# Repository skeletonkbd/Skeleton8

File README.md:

# Skeleton8

 This is a 4x2 macropad assuming PCBA with stacked acrylic case.

### Firmware here

https://github.com/skeletonkbd/qmk_firmware/tree/Skeleton8/keyboards/skeletonkbd/skeleton8

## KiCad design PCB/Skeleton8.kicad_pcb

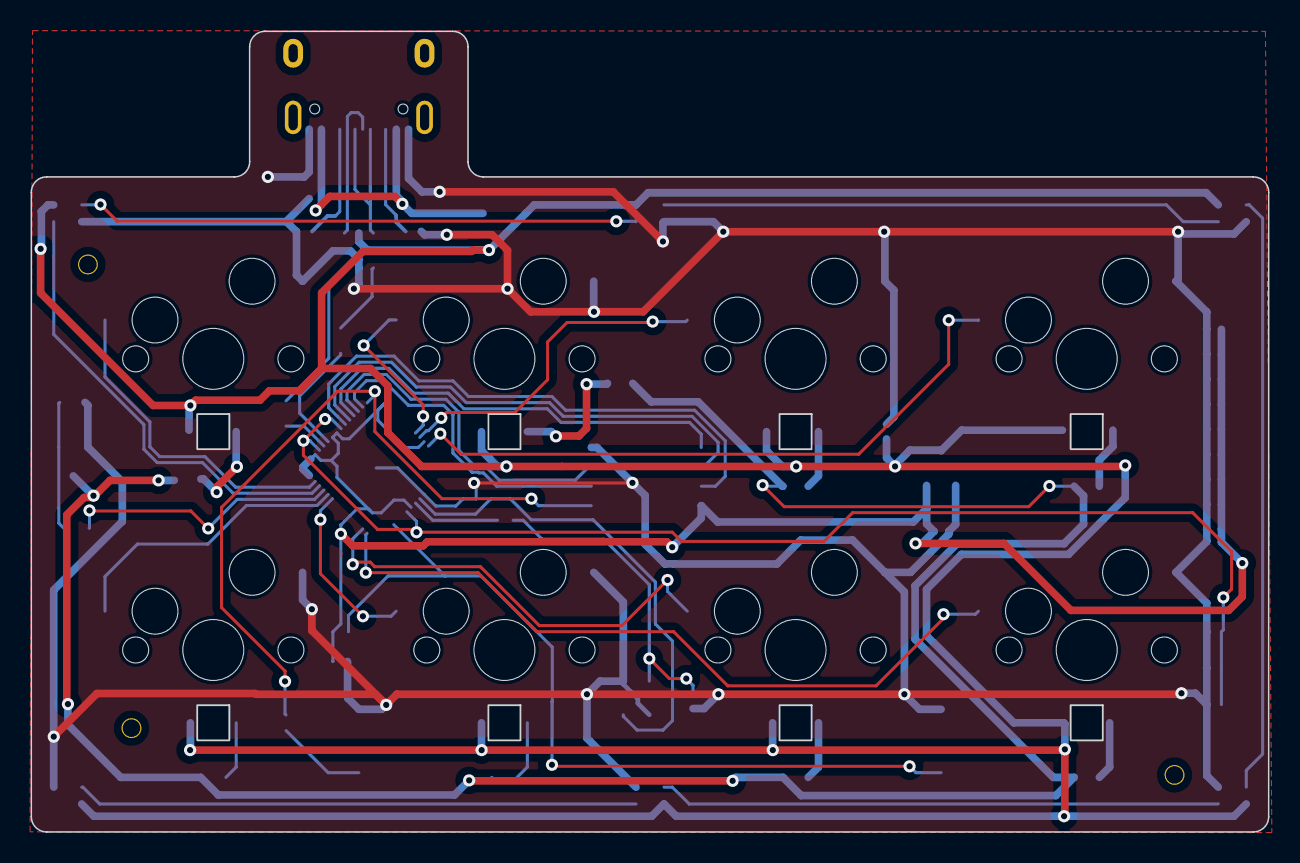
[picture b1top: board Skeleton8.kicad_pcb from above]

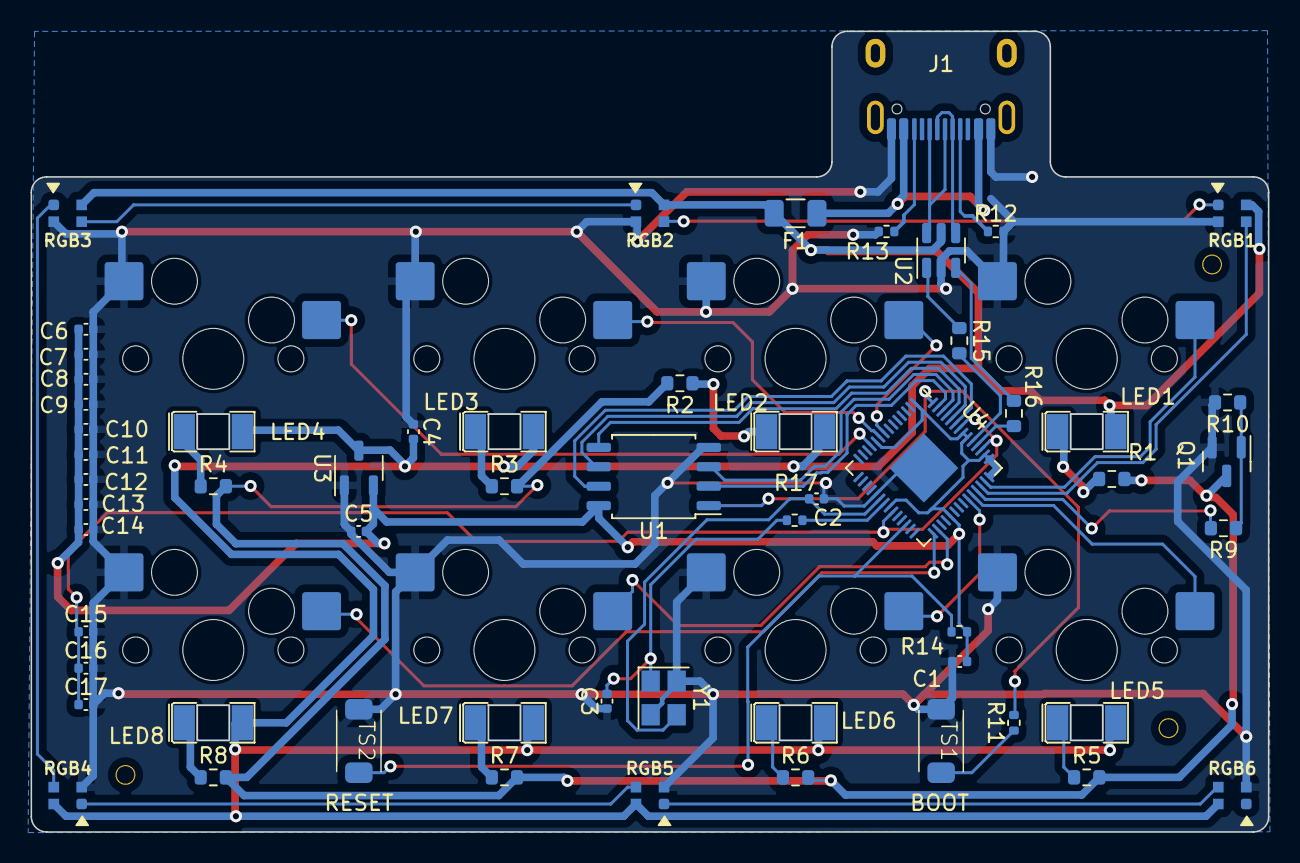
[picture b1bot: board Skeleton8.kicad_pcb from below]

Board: 2 copper layers, 80.9 x 52.4 mm, 69 parts (66 on the bottom side), 49 nets.

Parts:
C1, C8, C9, C10, C11, C12, C13, C14, C16, C17: 100nF; C_0402_1005Metric
C2, C3: 22pF; C_0402_1005Metric
C4, C5, C7, C15: 1uF; C_0402_1005Metric
C6: 10uF; C_0402_1005Metric
F1: 500mA; Fuse_1206_3216Metric
H1, H2, H3: Hole; ToolingHole
J1: TYPE-C-31-M-12; USB_C_Receptacle_Hroparts_TYPE-C-31-M-12
LED1, LED2, LED3, LED4, LED5, LED6, LED7, LED8: LTW-C230DS
Q1: SI2302; SOT-23
R1, R2, R3, R4, R5, R6, R7, R8: 150; R_0603_1608Metric
R9: 33; R_0603_1608Metric
R10: 10k; R_0603_1608Metric
R11, R14, R17: 1k; R_0402_1005Metric
R12, R13: 5k1; R_0402_1005Metric
R15, R16: 27; R_0603_1608Metric
RGB1, RGB2, RGB3, RGB4, RGB5, RGB6: WS2812B-2020; LED_WS2812_2020
SW1, SW2, SW3, SW4, SW5, SW6, SW7, SW8: SW_Push; MX-Hotswap-1U
TS1, TS2: SW_Push; TS-1088
U1: W25Q128JVS; SOIC-8_5.23x5.23mm_P1.27mm
U2: USBLC6-2SC6; SOT-23-6
U3: XC6206PxxxMR; SOT-23-3
U4: RP2040; QFN-56-1EP_7x7mm_P0.4mm_EP3.2x3.2mm
Y1: 12MHz; Crystal_SMD_3225-4Pin_3.2x2.5mm

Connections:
+1V1: C15.1, C16.1, C17.1, U4.23 (DVDD), U4.45 (VREG_VOUT), U4.50 (DVDD)
+3V3: C1.1, C5.2, C6.1, C7.1, C8.1, C9.1, C10.1, C11.1, C12.1, C13.1, C14.1, R14.1, U1.8 (VCC), U3.2 (VO), U4.1 (IOVDD), U4.10 (IOVDD), U4.22 (IOVDD), U4.33 (IOVDD), U4.42 (IOVDD), U4.43 (ADC_AVDD), U4.44 (VREG_IN), U4.48 (USB_VDD), U4.49 (IOVDD)
+5V: C4.2, F1.2, LED1.2 (A), LED2.2 (A), LED3.2 (A), LED4.2 (A), LED5.2 (A), LED6.2 (A), LED7.2 (A), LED8.2 (A), RGB1.4 (VDD), RGB2.4 (VDD), RGB3.4 (VDD), RGB4.4 (VDD), RGB5.4 (VDD), RGB6.4 (VDD), U2.5 (VBUS), U3.3 (VI)
/CC1: J1.A5 (CC1), R12.1
/CC2: J1.B5 (CC2), R13.1
/D_+: R15.2, U4.47 (USB_DP)
/D_-: R16.2, U4.46 (USB_DM)
/XTAL_O: C3.2, R17.1, Y1.1
/~USB_BOOT: R11.1, TS1.2
CS: R11.2, U1.1 (~CS), U4.56 (QSPI_SS)
D_N: R16.1, U2.3 (I/O2)
D_P: R15.1, U2.1 (I/O1)
D_USB_N: J1.A7 (D-), J1.B7 (D-), U2.4 (I/O2)
D_USB_P: J1.A6 (D+), J1.B6 (D+), U2.6 (I/O1)
GND: C1.2, C2.1, C3.1, C4.1, C5.1, C6.2, C7.2, C8.2, C9.2, C10.2, C11.2, C12.2, C13.2, C14.2, C15.2, C16.2, C17.2, J1.A1 (GND), J1.B1 (GND), Q1.2 (S), R10.2, R12.2, R13.2, RGB1.2 (VSS), RGB2.2 (VSS), RGB3.2 (VSS), RGB4.2 (VSS), RGB5.2 (VSS), RGB6.2 (VSS), SW1.2, SW2.2, SW3.2, SW4.2, SW5.2, SW6.2, SW7.2, SW8.2, TS1.1, TS2.1, U1.4 (GND), U2.2 (GND), U3.1 (GND), U4.19 (TESTEN), U4.57 (GND), Y1.2, Y1.4
unnamed: LED1.1 (K), R1.1
unnamed: LED2.1 (K), R2.1
unnamed: LED3.1 (K), R3.1
unnamed: LED4.1 (K), R4.1
unnamed: LED5.1 (K), R5.1
unnamed: LED6.1 (K), R6.1
unnamed: LED7.1 (K), R7.1
unnamed: LED8.1 (K), R8.1
unnamed: Q1.3 (D), R1.2, R2.2, R3.2, R4.2, R5.2, R6.2, R7.2, R8.2
unnamed: Q1.1 (G), R9.1, R10.1
unnamed: RGB1.1 (DOUT), RGB2.3 (DIN)
unnamed: RGB2.1 (DOUT), RGB3.3 (DIN)
unnamed: RGB3.1 (DOUT), RGB4.3 (DIN)
unnamed: RGB4.1 (DOUT), RGB5.3 (DIN)
unnamed: RGB5.1 (DOUT), RGB6.3 (DIN)
QSPI_CLK: U1.6 (CLK), U4.52 (QSPI_SCLK)
SD0: U1.5 (DI(IO0)), U4.53 (QSPI_SD0)
SD1: U1.2 (DO(IO1)), U4.55 (QSPI_SD1)
SD2: U1.3 (IO2), U4.54 (QSPI_SD2)
SD3: U1.7 (IO3), U4.51 (QSPI_SD3)
VBUS: F1.1, J1.A4 (VBUS), J1.B4 (VBUS)
XTAL_IN: C2.2, U4.20 (XIN), Y1.3
XTAL_OUT: R17.2, U4.21 (XOUT)
backlight: R9.2, U4.39 (GPIO27_ADC1)
key1: SW1.1, U4.41 (GPIO29_ADC3)
key2: SW2.1, U4.8 (GPIO6)
key3: SW3.1, U4.9 (GPIO7)
key4: SW4.1, U4.11 (GPIO8)
key5: SW5.1, U4.38 (GPIO26_ADC0)
key6: SW6.1, U4.37 (GPIO25)
key7: SW7.1, U4.30 (GPIO19)
key8: SW8.1, U4.29 (GPIO18)
underglow: RGB1.3 (DIN), U4.40 (GPIO28_ADC2)
~RESET: R14.2, TS2.2, U4.26 (RUN)

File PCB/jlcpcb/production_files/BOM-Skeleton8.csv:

Comment,Designator,Footprint,LCSC
1k,"R11,R14,R17",R_0402_1005Metric,C11702
W25Q128JVS,U1,SOIC-8_5.23x5.23mm_P1.27mm,C131025
100nF,"C1,C10,C11,C12,C13,C14,C16,C17,C8,C9",C_0402_1005Metric,C1525
10uF,C6,C_0402_1005Metric,C15525
22pF,"C2,C3",C_0402_1005Metric,C1555
RP2040,U4,QFN-56-1EP_7x7mm_P0.4mm_EP3.2x3.2mm,C2040
150,"R1,R2,R3,R4,R5,R6,R7,R8",R_0603_1608Metric,C22808
33,R9,R_0603_1608Metric,C23140
27,"R15,R16",R_0603_1608Metric,C25190
10k,R10,R_0603_1608Metric,C25804
5k1,"R12,R13",R_0402_1005Metric,C25905
USBLC6-2SC6,U2,SOT-23-6,C2827654
SI2302,Q1,SOT-23,C2891732
1uF,"C15,C4,C5,C7",C_0402_1005Metric,C52923
XC6206PxxxMR,U3,SOT-23-3,C5446
LTW-C230DS,"LED1,LED2,LED3,LED4,LED5,LED6,LED7,LED8",LTW-C230DS,C575513
500mA,F1,Fuse_1206_3216Metric,C70076
SW_Push,"TS1,TS2",TS-1088,C720477
12MHz,Y1,Crystal_SMD_3225-4Pin_3.2x2.5mm,C9002
TYPE-C-31-M-12,J1,USB_C_Receptacle_Hroparts_TYPE-C-31-M-12,

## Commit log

2024-01-09 pcba
